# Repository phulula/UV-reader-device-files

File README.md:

# UV-reader-device-files
schematic, PCB and source codes files for the UV reader device
#changes

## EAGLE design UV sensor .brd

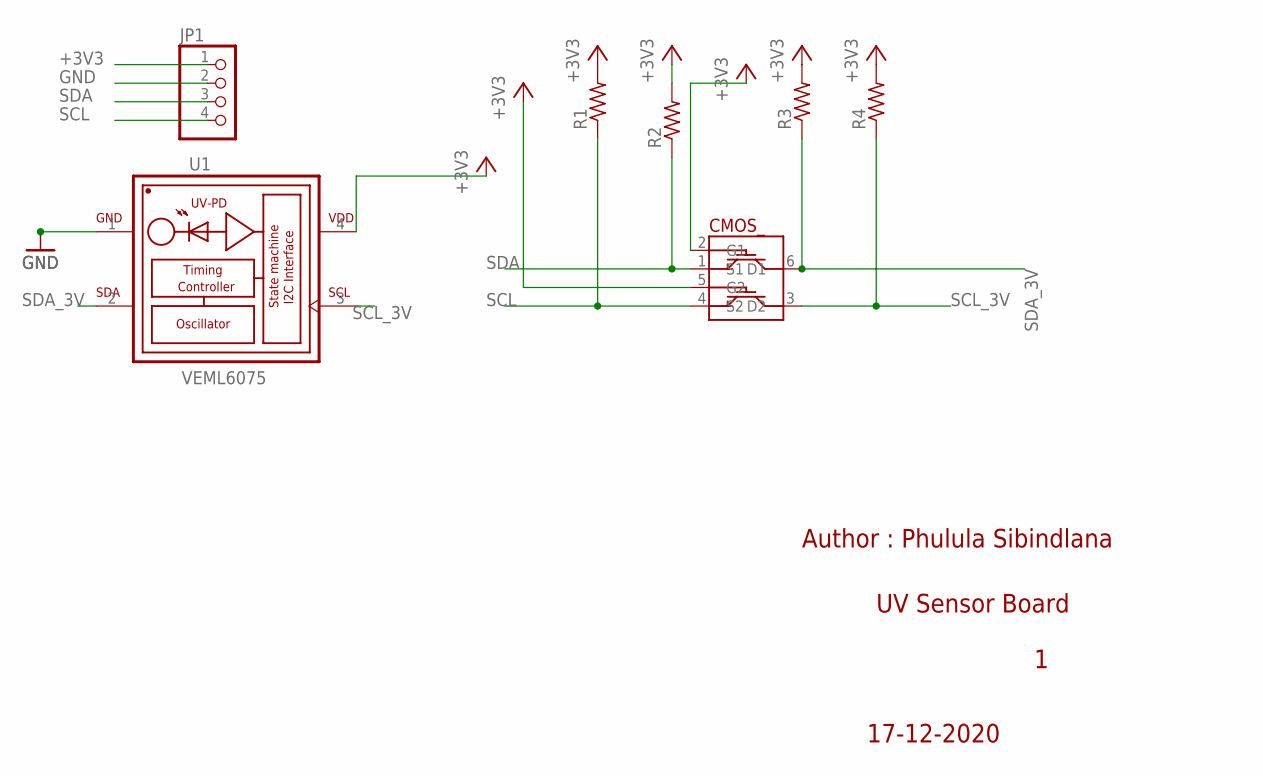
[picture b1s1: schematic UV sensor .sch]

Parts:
JP1: PINHD-1X4; 1X04
R1, R2, R3, R4: R-US_R0603; R0603
U1: VEML6075; VISHAY_VEML6075_1.25X2X1
U$1: 2N7002DW; SOT363

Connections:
+3V3: JP1.1, R1.2, R2.2, R3.2, R4.2, U1.4 (VDD), U$1.2 (G1)
GND: JP1.2, U1.1 (GND)
SCL: JP1.4, R1.1, U$1.4 (S2)
SCL_3V: R4.1, U1.3 (SCL), U$1.3 (D2)
SDA: JP1.3, R2.1, U$1.1 (S1)
SDA_3V: R3.1, U1.2 (SDA), U$1.6 (D1)

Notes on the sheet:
UV Sensor Board
17-12-2020
Author : Phulula Sibindlana

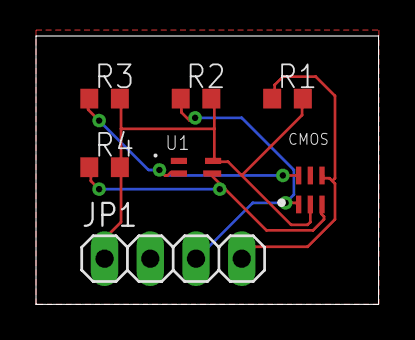
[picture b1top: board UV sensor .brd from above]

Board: 2 copper layers, 19.0 x 14.9 mm, 7 parts (0 on the bottom side), 6 nets.

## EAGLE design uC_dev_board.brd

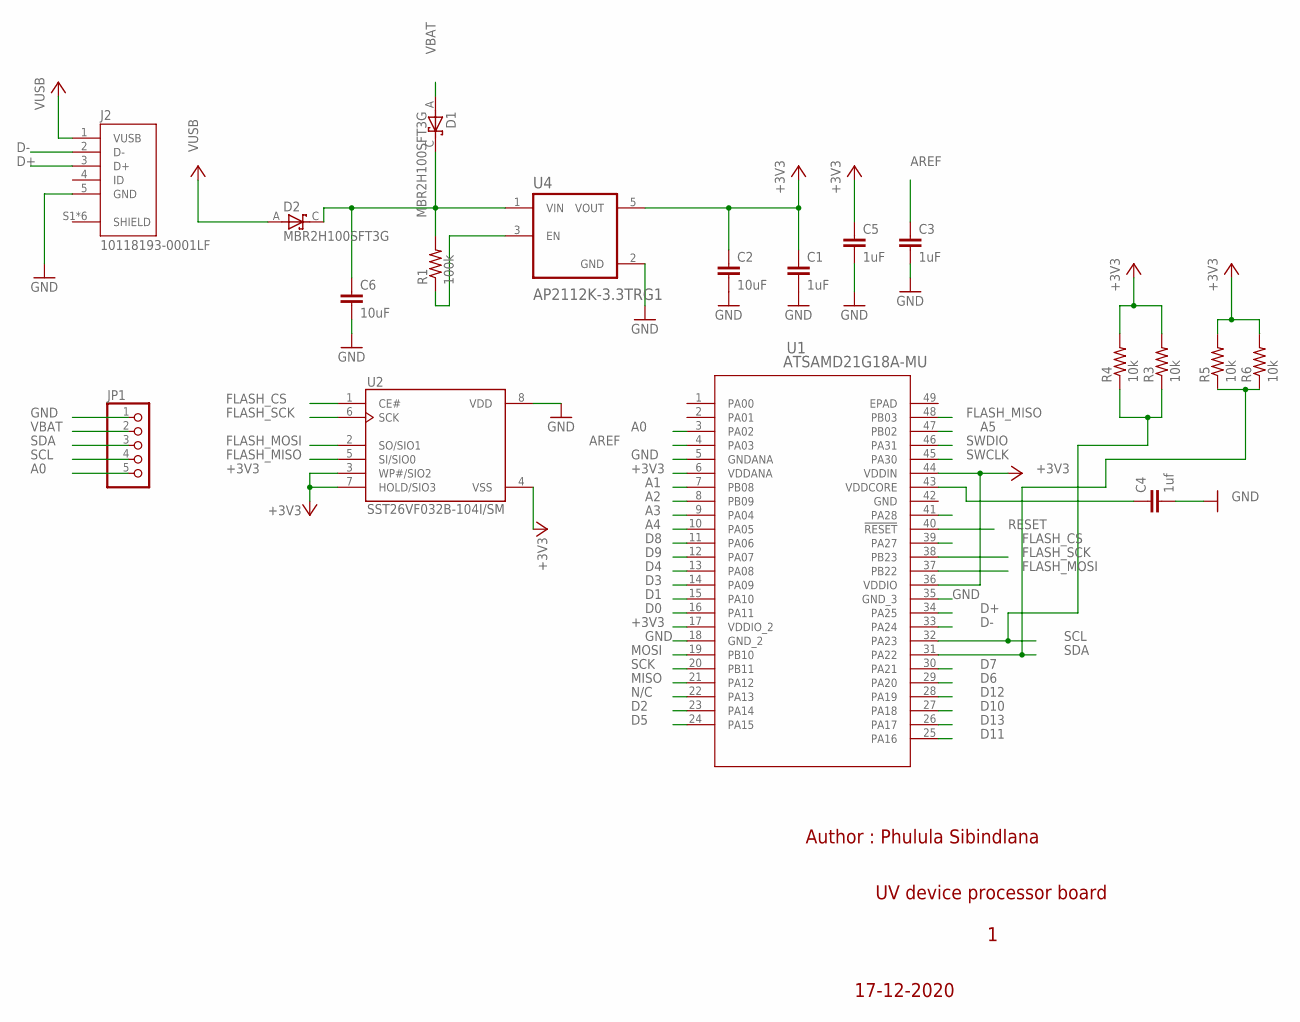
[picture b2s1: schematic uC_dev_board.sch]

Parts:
C1, C3, C5: 1uF; C0805
C2, C6: 10uF; C0805
C4: 1uf; C0805
D1, D2: MBR2H100SFT3G; SODFL3616X98N
J2: 10118193-0001LF; FCI_10118193-0001LF
JP1: PINHD-1X5; 1X05
R1: 100k; R0603
R3, R4, R5, R6: 10k; R0603
U1: ATSAMD21G18A-MU; QFN48_7X7MC_MCH
U2: SST26VF032B-104I/SM; SOIC127P794X203-8N
U4: AP2112K-3.3TRG1; SOT95P285X140-5N

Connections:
+3V3: C1.1, C2.1, C5.1, R3.2, R4.2, R5.2, R6.2, U1.6 (VDDANA), U1.17 (VDDIO_2), U1.36 (VDDIO), U1.44 (VDDIN), U2.3 (WP#/SIO2), U2.4 (VSS), U2.7 (HOLD/SIO3), U4.5 (VOUT)
+5V: D2.A, J2.1 (VUSB)
A0: JP1.5, U1.3 (PA02)
A1: U1.7 (PB08)
A2: U1.8 (PB09)
A3: U1.9 (PA04)
A4: U1.10 (PA05)
A5: U1.47 (PB02)
AREF: C3.1, U1.4 (PA03)
D0: U1.16 (PA11)
D1: U1.15 (PA10)
D2: U1.23 (PA14)
D3: U1.14 (PA09)
D4: U1.13 (PA08)
D5: U1.24 (PA15)
D6: U1.29 (PA20)
D7: U1.30 (PA21)
D8: U1.11 (PA06)
D9: U1.12 (PA07)
D10: U1.27 (PA18)
D11: U1.25 (PA16)
D12: U1.28 (PA19)
D13: U1.26 (PA17)
D+: J2.3 (D+), U1.34 (PA25)
D-: J2.2 (D-), U1.33 (PA24)
FLASH_CS: U1.39 (PA27), U2.1 (CE#)
FLASH_MISO: U1.48 (PB03), U2.5 (SI/SIO0)
FLASH_MOSI: U1.37 (PB22), U2.2 (SO/SIO1)
FLASH_SCK: U1.38 (PB23), U2.6 (SCK)
GND: C1.2, C2.2, C3.2, C4.2, C5.2, C6.2, J2.5 (GND), JP1.1, U1.5 (GNDANA), U1.18 (GND_2), U1.35 (GND_3), U2.8 (VDD), U4.2 (GND)
MISO: U1.21 (PA12)
MOSI: U1.19 (PB10)
unnamed: C6.1, D1.C, D2.C, R1.2, U4.1 (VIN)
unnamed: R1.1, U4.3 (EN)
unnamed: C4.1, U1.43 (VDDCORE)
N/C: U1.22 (PA13)
RESET: U1.40 (!RESET)
SCK: U1.20 (PB11)
SCL: JP1.4, R3.1, R4.1, U1.32 (PA23)
SDA: JP1.3, R5.1, R6.1, U1.31 (PA22)
SWCLK: U1.45 (PA30)
SWDIO: U1.46 (PA31)
VBAT: D1.A, JP1.2

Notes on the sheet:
UV device processor board
17-12-2020
Author : Phulula Sibindlana

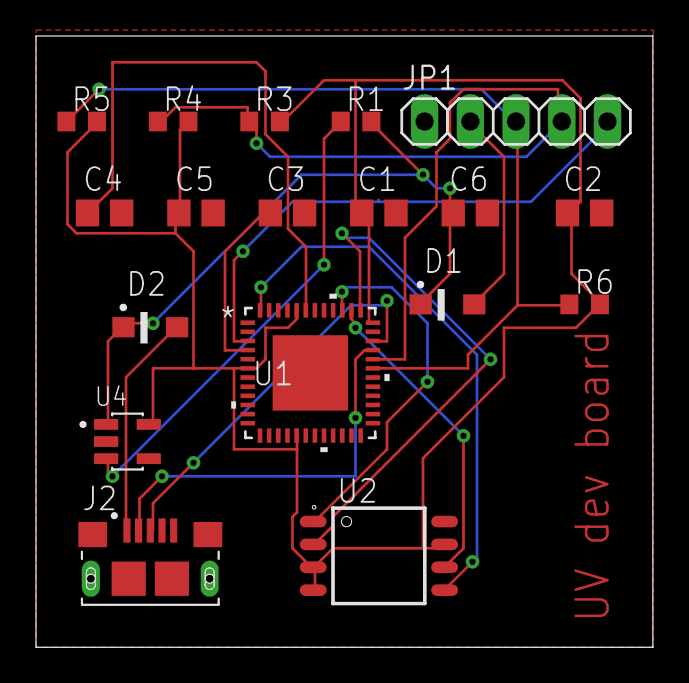
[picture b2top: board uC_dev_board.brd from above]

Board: 2 copper layers, 34.3 x 34.0 mm, 18 parts (0 on the bottom side), 17 nets.

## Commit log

2022-01-27 small trial
2022-05-15 new commit on new_branch

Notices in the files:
parts and their libraries:
COPYRIGHT: Copyright (C) 2018 Accelerated Designs. All rights reserved
